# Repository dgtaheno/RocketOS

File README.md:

# RocketOS

Open-source ESP32-S3 flight computer, telemetry, data-logging and validation platform for experimental model rockets.

---

## Project Status

RocketOS is currently at the **Mk1 prototype integration stage**.

The project has progressed from an ESP32 DevKitC development prototype to an ESP32-S3 N16R8 Mk1 architecture with two longitudinal prototype PCBs:

- **Main Deck v0.1 — 30 × 85.5 mm**
- **Power Deck v0.1 — 30 × 85.5 mm**

Both PCB designs have been released for prototype fabrication.

The current ESP32-S3 firmware builds successfully and the native regression suite passes **9/9 tests**.

The Mk1 electrical configuration is now being reproduced and validated on the bench before physical PCB bring-up.

Bench validation has confirmed simultaneous shared-I2C operation of:

- INA219 at `0x40`.
- GY-87 MPU-6050 at `0x68`.
- External BMP388 at `0x76`.
- GY-87 BMP180 at `0x77`.

The external BMP388 address was changed from its default `0x77` to `0x76` to resolve the address collision with the BMP180 present on the GY-87.

The fabricated Mk1 PCBs have **not yet been physically brought up or flight validated**.

---

## What RocketOS Does

RocketOS currently provides:

- Barometric altitude measurement.
- GPS position, altitude, speed and time.
- Autonomous flight-state detection.
- MicroSD flight logging.
- Buffered recovery from temporary SD write failures.
- Battery monitoring.
- Runtime system-health monitoring.
- Audible flight and system events.
- MAVLink telemetry over USB Serial.
- Flight-profile replay testing.
- Native automated regression tests.
- Serial replay on physical ESP32 hardware.

The target Mk1 ecosystem additionally includes:

- LoRa telemetry.
- GY-87 inertial sensing.
- Recovery actuation.
- Dedicated RocketOS Ground Station.
- Post-flight Flight Analyzer.

These target functions are not all implemented yet.

---

## Mk1 Hardware

### Main Deck v0.1

The Main Deck is based on the **ESP32-S3 N16R8** and provides interfaces for:

| Component | Model | Function |
|---|---|---|
| Microcontroller | ESP32-S3 N16R8 | Flight computer |
| GNSS | u-blox NEO-M9N | Position, altitude, speed and UTC |
| Barometer | BMP388 at I2C `0x76` | Pressure, temperature and altitude |
| Storage | MicroSD | Flight-data logging |
| IMU module | GY-87 | Future inertial sensing |
| Radio | Ai-Thinker Ra-02 / SX1278 | Future LoRa telemetry |
| Audible feedback | Active buzzer | Status and recovery beacon |

The external BMP388 is fixed at I2C address **`0x76`** by tying SDO to GND. This avoids the **`0x77`** address used by the BMP180 present on the Mk1 GY-87 module.

The already-released Main Deck v0.1 fabrication package predates this correction and leaves BMP388 SDO unconnected. Fabricated v0.1 boards therefore require an **SDO-to-GND rework** during assembly. The current KiCad source includes the corrected connection.

Main Deck envelope:

```text
30 × 85.5 mm
```

#### Main Deck module references

| ESP32-S3 N16R8 | BMP388 | NEO-M9N |
|---|---|---|
|  |  |  |

| MicroSD | GY-87 | Ra-02 / SX1278 |
|---|---|---|
|  |  |  |

| Active buzzer |
|---|
|  |

### Power Deck v0.1

The Power Deck provides:

- XT30 battery input.
- 2 A resettable protection fuse.
- Main power switching.
- INA219 voltage/current monitoring.
- MP1584 regulation.
- 5 V output to the Main Deck.
- INA219 I2C connection to the Main Deck.
- Bulk and local decoupling.

Power Deck envelope:

```text
30 × 85.5 mm
```

#### Power Deck module references

| INA219 | MP1584 |
|---|---|
|  |  |

### Battery

Current Mk1 development battery:

```text
Tattu 2S 550 mAh LiPo
7.4 V nominal
8.4 V maximum
```

The battery is mechanically retained independently of the PCBs.

### Mk1 Schematics

The current Mk1 electrical architecture is split between two longitudinal PCBs.

#### Main Deck v0.1

#### Power Deck v0.1

The schematic SVGs are exported from the current KiCad source.

Earlier `flighttelemetry-v*.png` schematics are retained in `docs/schematics/` for historical traceability and do not represent the current Mk1 architecture.

---

## Mk1 Architecture

```text
                     2S LiPo
                        |
                        v
              +-------------------+
              |    Power Deck     |
              |                   |
              | PPTC Protection   |
              | Main Switch       |
              | INA219            |
              | MP1584            |
              +---------+---------+
                        |
               +5V / I2C / GND
                        |
                        v
              +-------------------+
              |     Main Deck     |
              |                   |
              | ESP32-S3 N16R8    |
              | BMP388 @ 0x76     |
              | NEO-M9N           |
              | MicroSD           |
              | GY-87             |
              | Ra-02 / SX1278    |
              | Active Buzzer     |
              +---------+---------+
                        |
              +---------+---------+
              |                   |
              v                   v
          SD Logging       Flight Processing
                                  |
                         +--------+--------+
                         |                 |
                         v                 v
                   USB MAVLink       LoRa Transport
                   implemented          planned
```

The two PCBs are designed for longitudinal installation in a mechanical sled.

The final sled geometry remains under development.

---

## Mk1 GPIO Baseline

| Function | ESP32-S3 GPIO |
|---|---:|
| GPS RX | 17 |
| GPS TX | 18 |
| I2C SDA | 8 |
| I2C SCL | 9 |
| SPI MOSI | 11 |
| SPI MISO | 13 |
| SPI SCK | 12 |
| MicroSD CS | 5 |
| LoRa NSS | 10 |
| LoRa RESET | 14 |
| LoRa DIO0 | 15 |
| Buzzer control | 21 |

MicroSD and LoRa share the SPI bus and use independent chip-select signals.

Integrated MicroSD + LoRa operation still requires bench validation.

DS18B20 support remains in the firmware but is disabled in the current Mk1 configuration.

---

## Mk1 I2C Baseline

The Mk1 shared I2C bus has been bench validated with the current module set:

| Device | Address | Status |
|---|---:|---|
| INA219 | `0x40` | Detected |
| GY-87 MPU-6050 | `0x68` | Detected and identified |
| External BMP388 | `0x76` | Detected and flight-firmware validated |
| GY-87 BMP180 | `0x77` | Detected and identified |

The external BMP388 uses SDO tied to GND to select address `0x76`.

This establishes electrical coexistence on the shared bus. GY-87 sensor acquisition is not yet integrated into the flight firmware.

---

## Flight-State Detection

RocketOS implements the following flight-state sequence:

```text
IDLE -> BOOST -> COAST -> APOGEE -> DESCENT -> LANDED
```

Detection currently uses BMP388 barometric altitude and derived climb rate.

This provides **flight-event detection**, not recovery deployment control.

Recovery actuation remains planned.

---

## Logging

RocketOS currently supports:

- Automatic CSV log creation.
- GPS timestamp filenames when GPS time is available.
- Boot-number filename fallback.
- Flight and sensor data recording.
- SD startup self-test.
- Runtime SD failure detection.
- 100-record RAM FIFO.
- Ordered recovery after temporary SD failures.
- Runtime event logging.

Onboard logging operates independently from the telemetry transport.

---

## Telemetry

### MAVLink

MAVLink telemetry is currently implemented over USB Serial.

Implemented messages include:

| Message | Purpose |
|---|---|
| HEARTBEAT | Vehicle presence and link status |
| SYS_STATUS | System and battery status |
| GPS_RAW_INT | GNSS position and fix |
| GLOBAL_POSITION_INT | Position and relative altitude |
| GLOBAL_POSITION_INT_COV | Position with covariance |
| VFR_HUD | Speed, altitude and climb rate |
| BATTERY_STATUS | Battery voltage, current and SOC |
| HOME_POSITION | Home reference |
| STATUSTEXT | System and flight events |

### LoRa

Mk1 radio hardware:

```text
Ai-Thinker Ra-02
SX1278-class
```

The radio interface is present in the Main Deck v0.1 hardware design.

LoRa transport is **not yet implemented in the flight firmware**.

---

## Flight Profile Replay Testing

RocketOS supports data-driven testing using altitude-vs-time flight profiles.

```text
CSV flight profile
        |
        v
FlightStateMachine
        |
        v
Detected flight sequence
        |
        v
Expected result validation
```

Current profiles:

| Profile | Expected Apogee | Purpose |
|---|---:|---|
| `estes_c6` | 253.9 m | Nominal flight |
| `midpower_machdip` | 904.4 m | Barometric Mach-dip rejection |
| `low_apogee` | 71.5 m | Low-altitude flight |

Current native regression result:

```text
9 test cases
9 succeeded
```

The suite contains:

- 3 flight-profile tests.
- 6 flight-state-machine tests.

Run it with:

```bash
cd firmware/flight-computer
pio test -e native
```

If PlatformIO is not available globally on Windows, the project development environment can be invoked directly:

```powershell
& "$env:USERPROFILE\.platformio\penv\Scripts\pio.exe" test -d "firmware\flight-computer" -e native
```

---

## ESP32-S3 Firmware

The Mk1 firmware contains an ESP32-S3 N16R8 PlatformIO target.

Build with:

```powershell
& "$env:USERPROFILE\.platformio\penv\Scripts\pio.exe" run -d "firmware\flight-computer" -e esp32s3_n16r8
```

Current validation:

```text
Build: SUCCESS
Tests: 9 / 9 passed
```

Physical hardware identification of the current development module confirmed:

```text
ESP32-S3
240 MHz
16 MB flash
~8 MiB PSRAM
```

Build success does not establish complete Mk1 hardware validation.

---

## Battery Monitoring

The Mk1 BatteryMonitor uses a 2S LiPo baseline:

| Voltage | Estimated SOC |
|---:|---:|
| 8.40 V | 100% |
| 8.20 V | 90% |
| 8.00 V | 80% |
| 7.80 V | 70% |
| 7.60 V | 60% |
| 7.40 V | 50% |
| 7.20 V | 40% / Warning |
| 7.00 V | 25% |
| 6.80 V | 10% / Critical |
| 6.60 V | 0% |

Below 5.0 V is treated as battery disconnected.

Bench validation on the historical development configuration demonstrated:

- USB-powered, LiPo disconnected: approximately 4.10–4.13 V → `DISCONNECTED`.
- 2S LiPo connected: approximately 7.72–7.90 V → `CONNECTED / OK`.

This validates the BatteryMonitor behavior.

It does **not** validate the complete Mk1 Power Deck.

---

## Current Validation Boundary

### Validated

- Core flight firmware.
- ESP32-S3 firmware compilation.
- Physical ESP32-S3 N16R8 module identification.
- Native regression suite: 9/9.
- Flight-state-machine behavior.
- Flight-profile replay.
- Historical physical ESP32 replay.
- 2S BatteryMonitor behavior.
- Main Deck v0.1 PCB design release.
- Power Deck v0.1 PCB design release.
- Mk1 BMP388 on GPIO8/GPIO9 I2C bus.
- Mk1 MicroSD on GPIO11/GPIO12/GPIO13 with GPIO5 CS.
- Mk1 NEO-M9N on GPIO17/GPIO18.
- Shared-I2C electrical coexistence of INA219, MPU-6050, BMP388 and BMP180.
- BMP388 address correction to `0x76`.
- BMP388 + MicroSD + GPS simultaneous flight-firmware startup.
- MicroSD flight-log creation.
- GPS fix acquisition on the Mk1 bench configuration.

### Pending

- Buzzer circuit bench validation.
- Ra-02 bench validation.
- Shared MicroSD + Ra-02 SPI operation.
- Complete Power Deck topology bench validation.
- Main Deck physical PCB bring-up.
- Power Deck physical PCB bring-up.
- GY-87 firmware integration.
- LoRa radio communication.
- Complete integrated Mk1 bench validation.
- Mechanical sled validation.
- Recovery actuation.
- Real-flight validation.

RocketOS Mk1 is therefore a **prototype under integration**, not a flight-qualified system.

---

## Prototype PCB Status

Main Deck v0.1 and Power Deck v0.1 have been released for prototype fabrication.

Manufacturing baseline:

```text
PCB:        FR4
Layers:     2
Size:       30 × 85.5 mm
Thickness:  1.6 mm
Copper:     1 oz
Finish:     Lead-free HASL
Mask:       Green
Silkscreen: White
```

Prototype order:

```text
5 × Main Deck v0.1
5 × Power Deck v0.1
```

The exact manufacturing packages are retained in the repository.

The released Main Deck v0.1 fabrication package leaves BMP388 SDO unconnected. The five fabricated Main Deck v0.1 boards therefore require an **SDO-to-GND rework** when the BMP388 is installed.

The current KiCad source contains the corrected SDO-to-GND connection.

The released v0.1 fabrication package remains unchanged to preserve exact as-built traceability.

Fabrication release does not imply electrical or flight validation.

---

## Repository Structure

```text
RocketOS/
|
+-- docs/
|   +-- Baseline/
|   +-- images/
|   +-- schematics/
|
+-- firmware/
|   +-- flight-computer/
|   +-- hardware-id-test/
|
+-- hardware/
|   +-- Mk1/
|       +-- Main_Deck_Longitudinal_v0.1/
|       +-- Power_Deck_Longitudinal/
|       +-- superseded/
|
+-- README.md
```

The authoritative project baseline is maintained under:

```text
docs/Baseline/
```

Key documents:

- `RocketOS_Master_Context.md`
- `RocketOS_Architecture.md`
- `RocketOS_System_Requirements.md`
- `RocketOS_Project_History.md`

Repository code, repeatable validation evidence and released hardware artifacts take precedence when determining implementation status.

---

## Development Principles

RocketOS prioritizes:

1. Reliability over unnecessary complexity.
2. Commercial modules before unnecessary custom hardware.
3. Validation before optimization.
4. Modularity.
5. Maintainability.
6. Field repairability.
7. Cost awareness.
8. Proven solutions over experimental complexity.

The project intentionally distinguishes between:

```text
IMPLEMENTED
DESIGN RELEASED
BENCH VALIDATED
PHYSICALLY INTEGRATED
FLIGHT VALIDATED
```

These states are not interchangeable.

---

## Next Milestones

The immediate development sequence is:

```text
1. Validate buzzer transistor circuit
2. Validate Ra-02
3. Validate shared MicroSD + Ra-02 SPI bus
4. Validate complete Power Deck topology on the bench
5. Receive and inspect prototype PCBs
6. Bring up fabricated Power Deck
7. Bring up fabricated Main Deck, including BMP388 SDO-to-GND rework
8. Develop and validate longitudinal mechanical sled
9. Integrate GY-87 firmware acquisition
10. Integrate LoRa telemetry firmware
11. Complete integrated Mk1 bench validation
12. Real-flight validation
```

---

## License

MIT License

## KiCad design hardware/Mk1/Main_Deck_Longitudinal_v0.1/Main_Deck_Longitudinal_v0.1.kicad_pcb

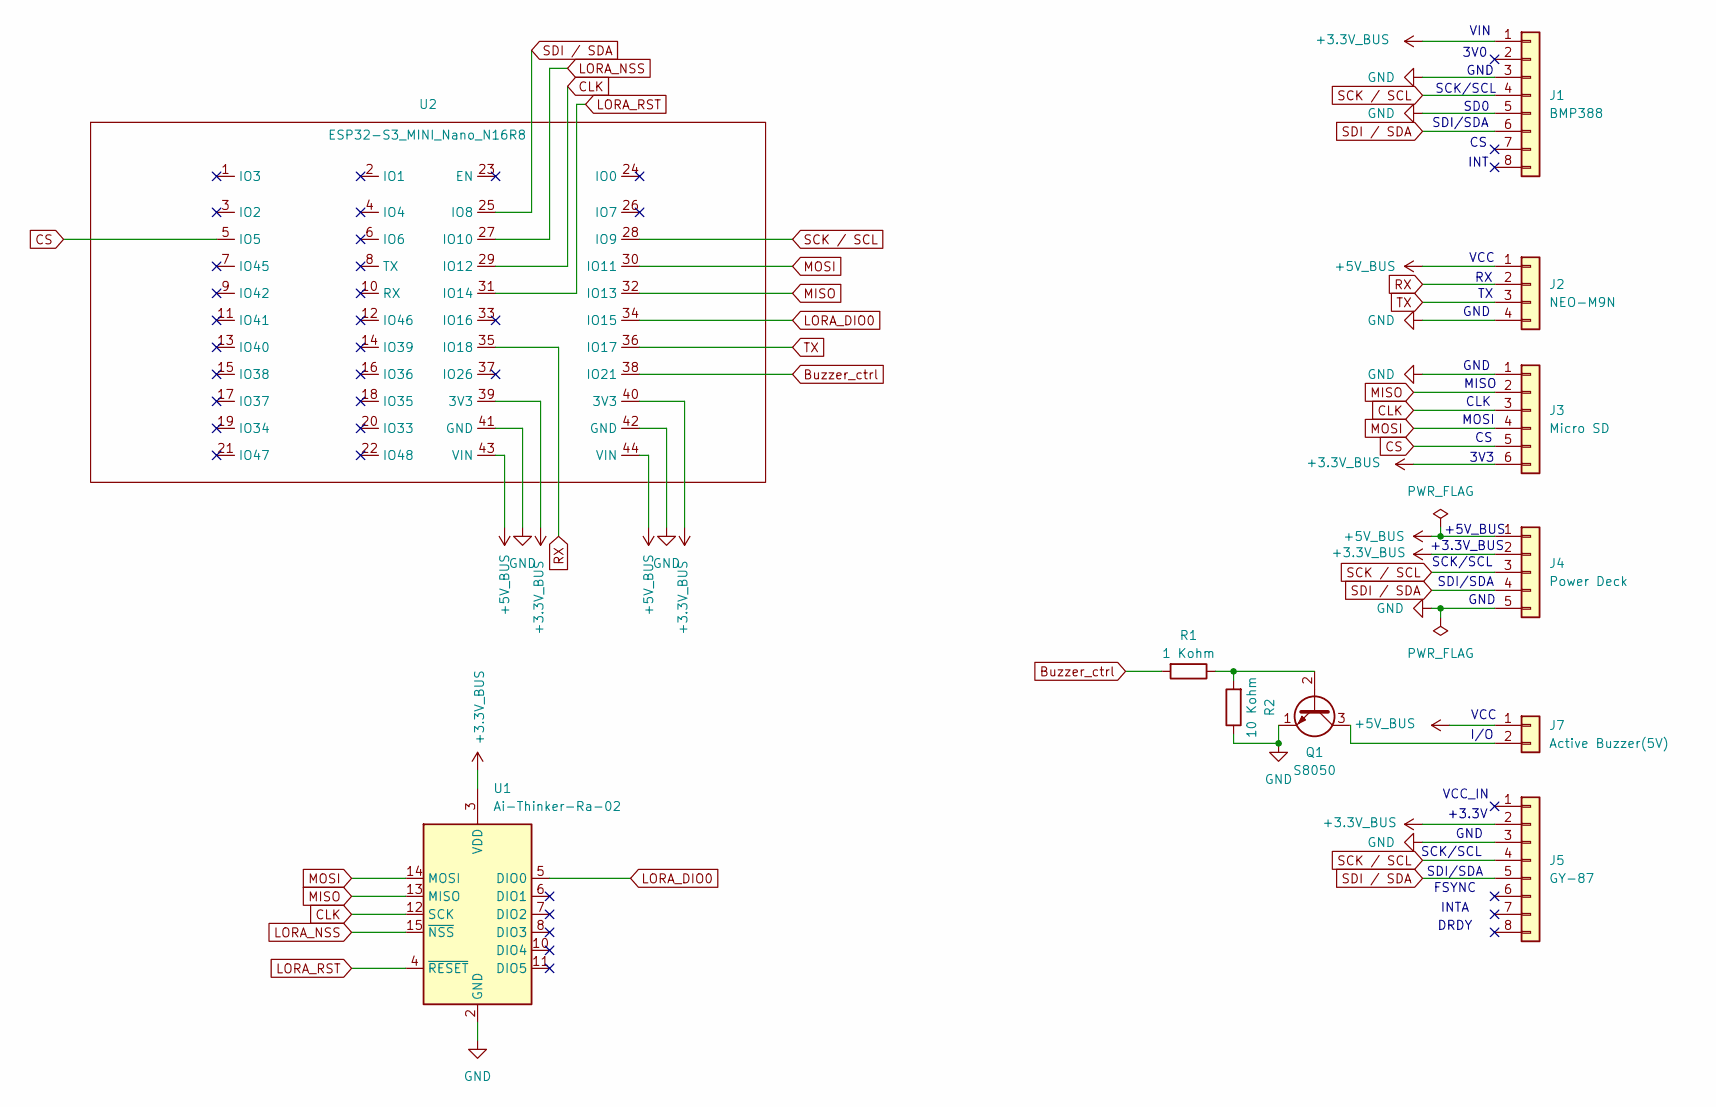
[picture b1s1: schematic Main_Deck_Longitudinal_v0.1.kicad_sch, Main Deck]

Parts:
J1: BMP388; BMP388_MODULE
J2: NEO-M9N; NEO_M9N_MODULE
J3: Micro SD; MicroSD
J4: Power Deck; JST_XH_B5B-XH-A_1x05_P2.50mm_Vertical
J5: GY-87; GY87
J7: Active Buzzer(5V); Buzzer_12x9.5RM7.6
Q1: S8050; TO-92_Inline
R1: 1 Kohm; R_Axial_DIN0207_L6.3mm_D2.5mm_P7.62mm_Horizontal
R2: 10 Kohm; R_Axial_DIN0207_L6.3mm_D2.5mm_P7.62mm_Horizontal
U1: Ai-Thinker-Ra-02; Ra-02_SX1278
U2: ESP32-S3_MINI_Nano_N16R8

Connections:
+3.3V_BUS: J1.1, J3.6, J4.2, J5.2, U1.3 (VDD), U2.39 (3V3), U2.40 (3V3)
+5V_BUS: J2.1, J4.1, J7.1, U2.43 (VIN), U2.44 (VIN)
Buzzer_ctrl: R1.2, U2.38 (IO21)
CLK: J3.3, U1.12 (SCK), U2.29 (IO12)
CS: J3.5, U2.5 (IO5)
GND: J1.3, J1.5, J2.4, J3.1, J4.5, J5.3, Q1.1 (E), R2.1, U1.1 (GND), U1.2 (GND), U1.9 (GND), U1.16 (GND), U2.41 (GND), U2.42 (GND)
LORA_DIO0: U1.5 (DIO0), U2.34 (IO15)
LORA_NSS: U1.15 (~NSS), U2.27 (IO10)
LORA_RST: U1.4 (~RESET), U2.31 (IO14)
MISO: J3.2, U1.13 (MISO), U2.32 (IO13)
MOSI: J3.4, U1.14 (MOSI), U2.30 (IO11)
unnamed: J7.2, Q1.3 (C)
unnamed: Q1.2 (B), R1.1, R2.2
RX: J2.2, U2.35 (IO18)
SCK / SCL: J1.4, J4.3, J5.4, U2.28 (IO9)
SDI / SDA: J1.6, J4.4, J5.5, U2.25 (IO8)
TX: J2.3, U2.36 (IO17)

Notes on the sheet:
SDI/SDA
GND
VCC
3V0
INT
VCC_IN
SCK/SCL
+3.3V
CLK
3V3
MISO
+3.3V_BUS
DRDY
SD0
VIN
MOSI
FSYNC
+5V_BUS
INTA
I/O

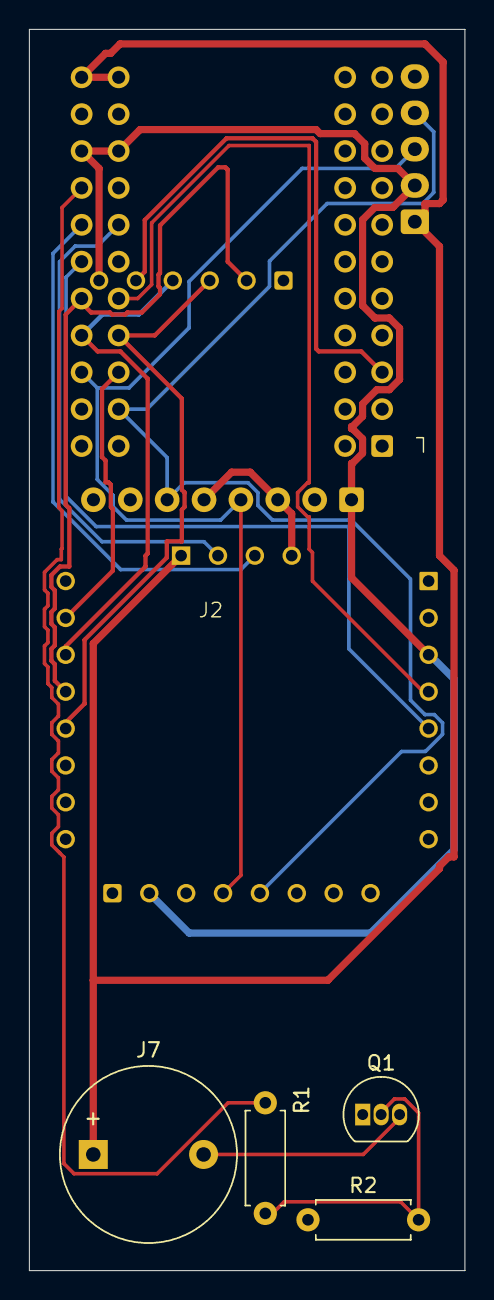
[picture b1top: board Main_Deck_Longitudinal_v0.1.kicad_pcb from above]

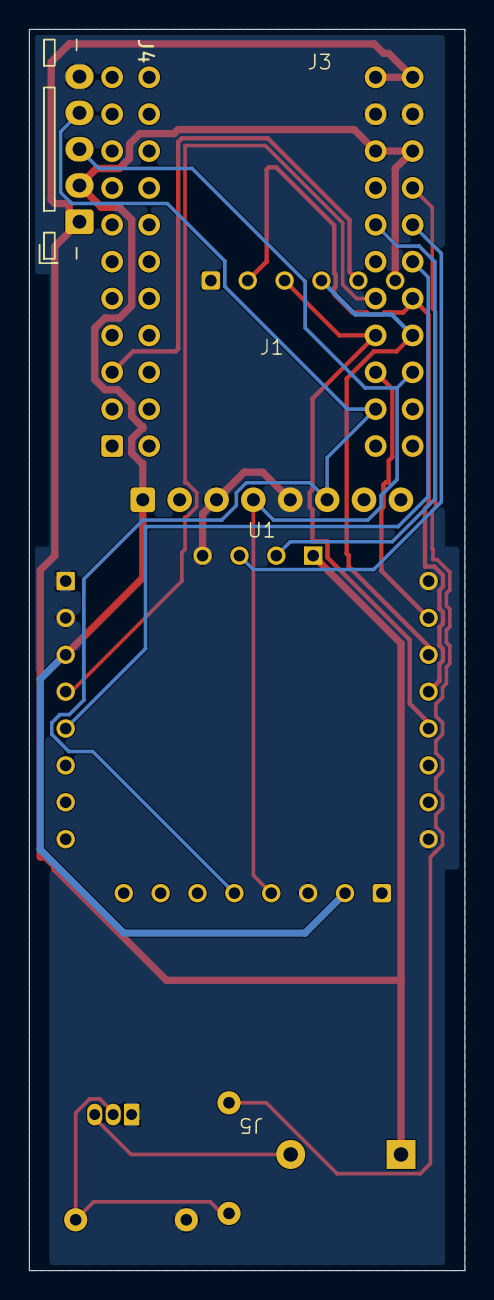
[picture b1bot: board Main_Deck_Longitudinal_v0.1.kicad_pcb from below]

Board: 2 copper layers, 30.0 x 85.5 mm, 11 parts (5 on the bottom side), 17 nets.

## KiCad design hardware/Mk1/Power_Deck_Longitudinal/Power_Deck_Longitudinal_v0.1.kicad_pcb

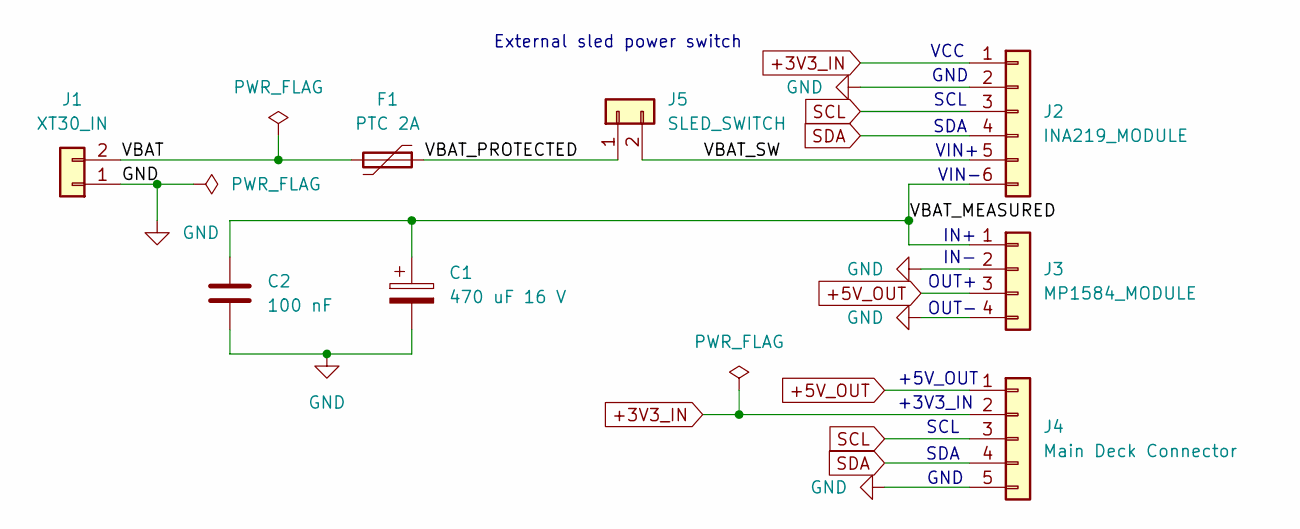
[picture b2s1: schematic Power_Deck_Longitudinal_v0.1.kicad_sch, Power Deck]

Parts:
C1: 470 uF 16 V; CP_Radial_D8.0mm_P3.50mm
C2: 100 nF; C_Disc_D5.0mm_W2.5mm_P5.00mm
F1: PTC 2A; JK30_200
J1: XT30_IN; XT30PW_F_RocketOS
J2: INA219_MODULE
J3: MP1584_MODULE; MP1584
J4: Main Deck Connector; JST_XH_B5B-XH-A_1x05_P2.50mm_Vertical
J5: SLED_SWITCH; JST_XH_B2B-XH-A_1x02_P2.50mm_Vertical

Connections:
+3V3_IN: J2.1, J4.2
+5V_OUT: J3.3, J4.1
/VBAT: F1.2, J1.2
/VBAT_MEASURED: C1.1, C2.1, J2.6, J3.1
/VBAT_PROTECTED: F1.1, J5.1
/VBAT_SW: J2.5, J5.2
GND: C1.2, C2.2, J1.1, J2.2, J3.2, J3.4, J4.5
SCL: J2.3, J4.3
SDA: J2.4, J4.4

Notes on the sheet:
SCL
IN-
OUT+
External sled power switch
VIN+
GND
IN+
OUT-
+3V3_IN
SDA
+5V_OUT
VCC
VIN-

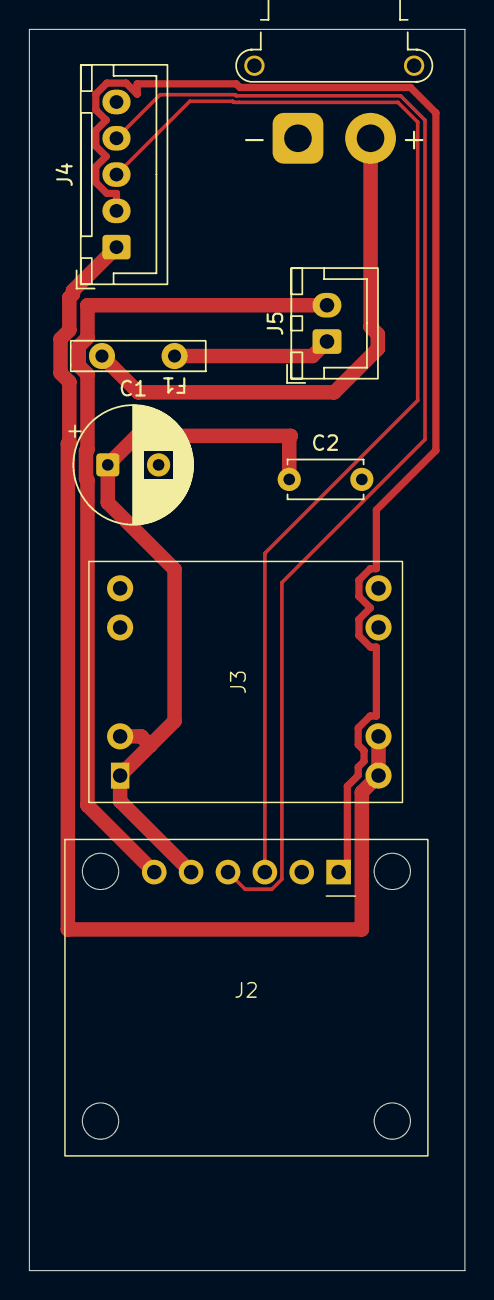
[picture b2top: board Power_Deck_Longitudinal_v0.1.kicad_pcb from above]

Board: 2 copper layers, 30.0 x 85.5 mm, 8 parts (0 on the bottom side), 9 nets.
